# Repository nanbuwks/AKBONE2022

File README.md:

# AKBONE2022

秋葉原ロボット部のトレーニングボード。
2022リリースはLEDパネルキットです。

初期コンセプトとAlpha版の説明
「AKBONE2022 で LED パネルを使ったオープンソーストレーニングキットを考える」
https://qiita.com/nanbuwks/items/5271dedf196623d452a0

AVTOKYO2022で頒布したBeta1版の説明
「LEDパネルキットAKBONE2022で楽しもう！ Beta1版」
https://qiita.com/nanbuwks/items/4317031bdf3bdcfafbf8

AKBONE2022の開発環境構築
「LEDパネルキット AKBONE2022 の環境構築を自分でやってみる
https://qiita.com/nanbuwks/items/d4523ebfb9cabdae90c5

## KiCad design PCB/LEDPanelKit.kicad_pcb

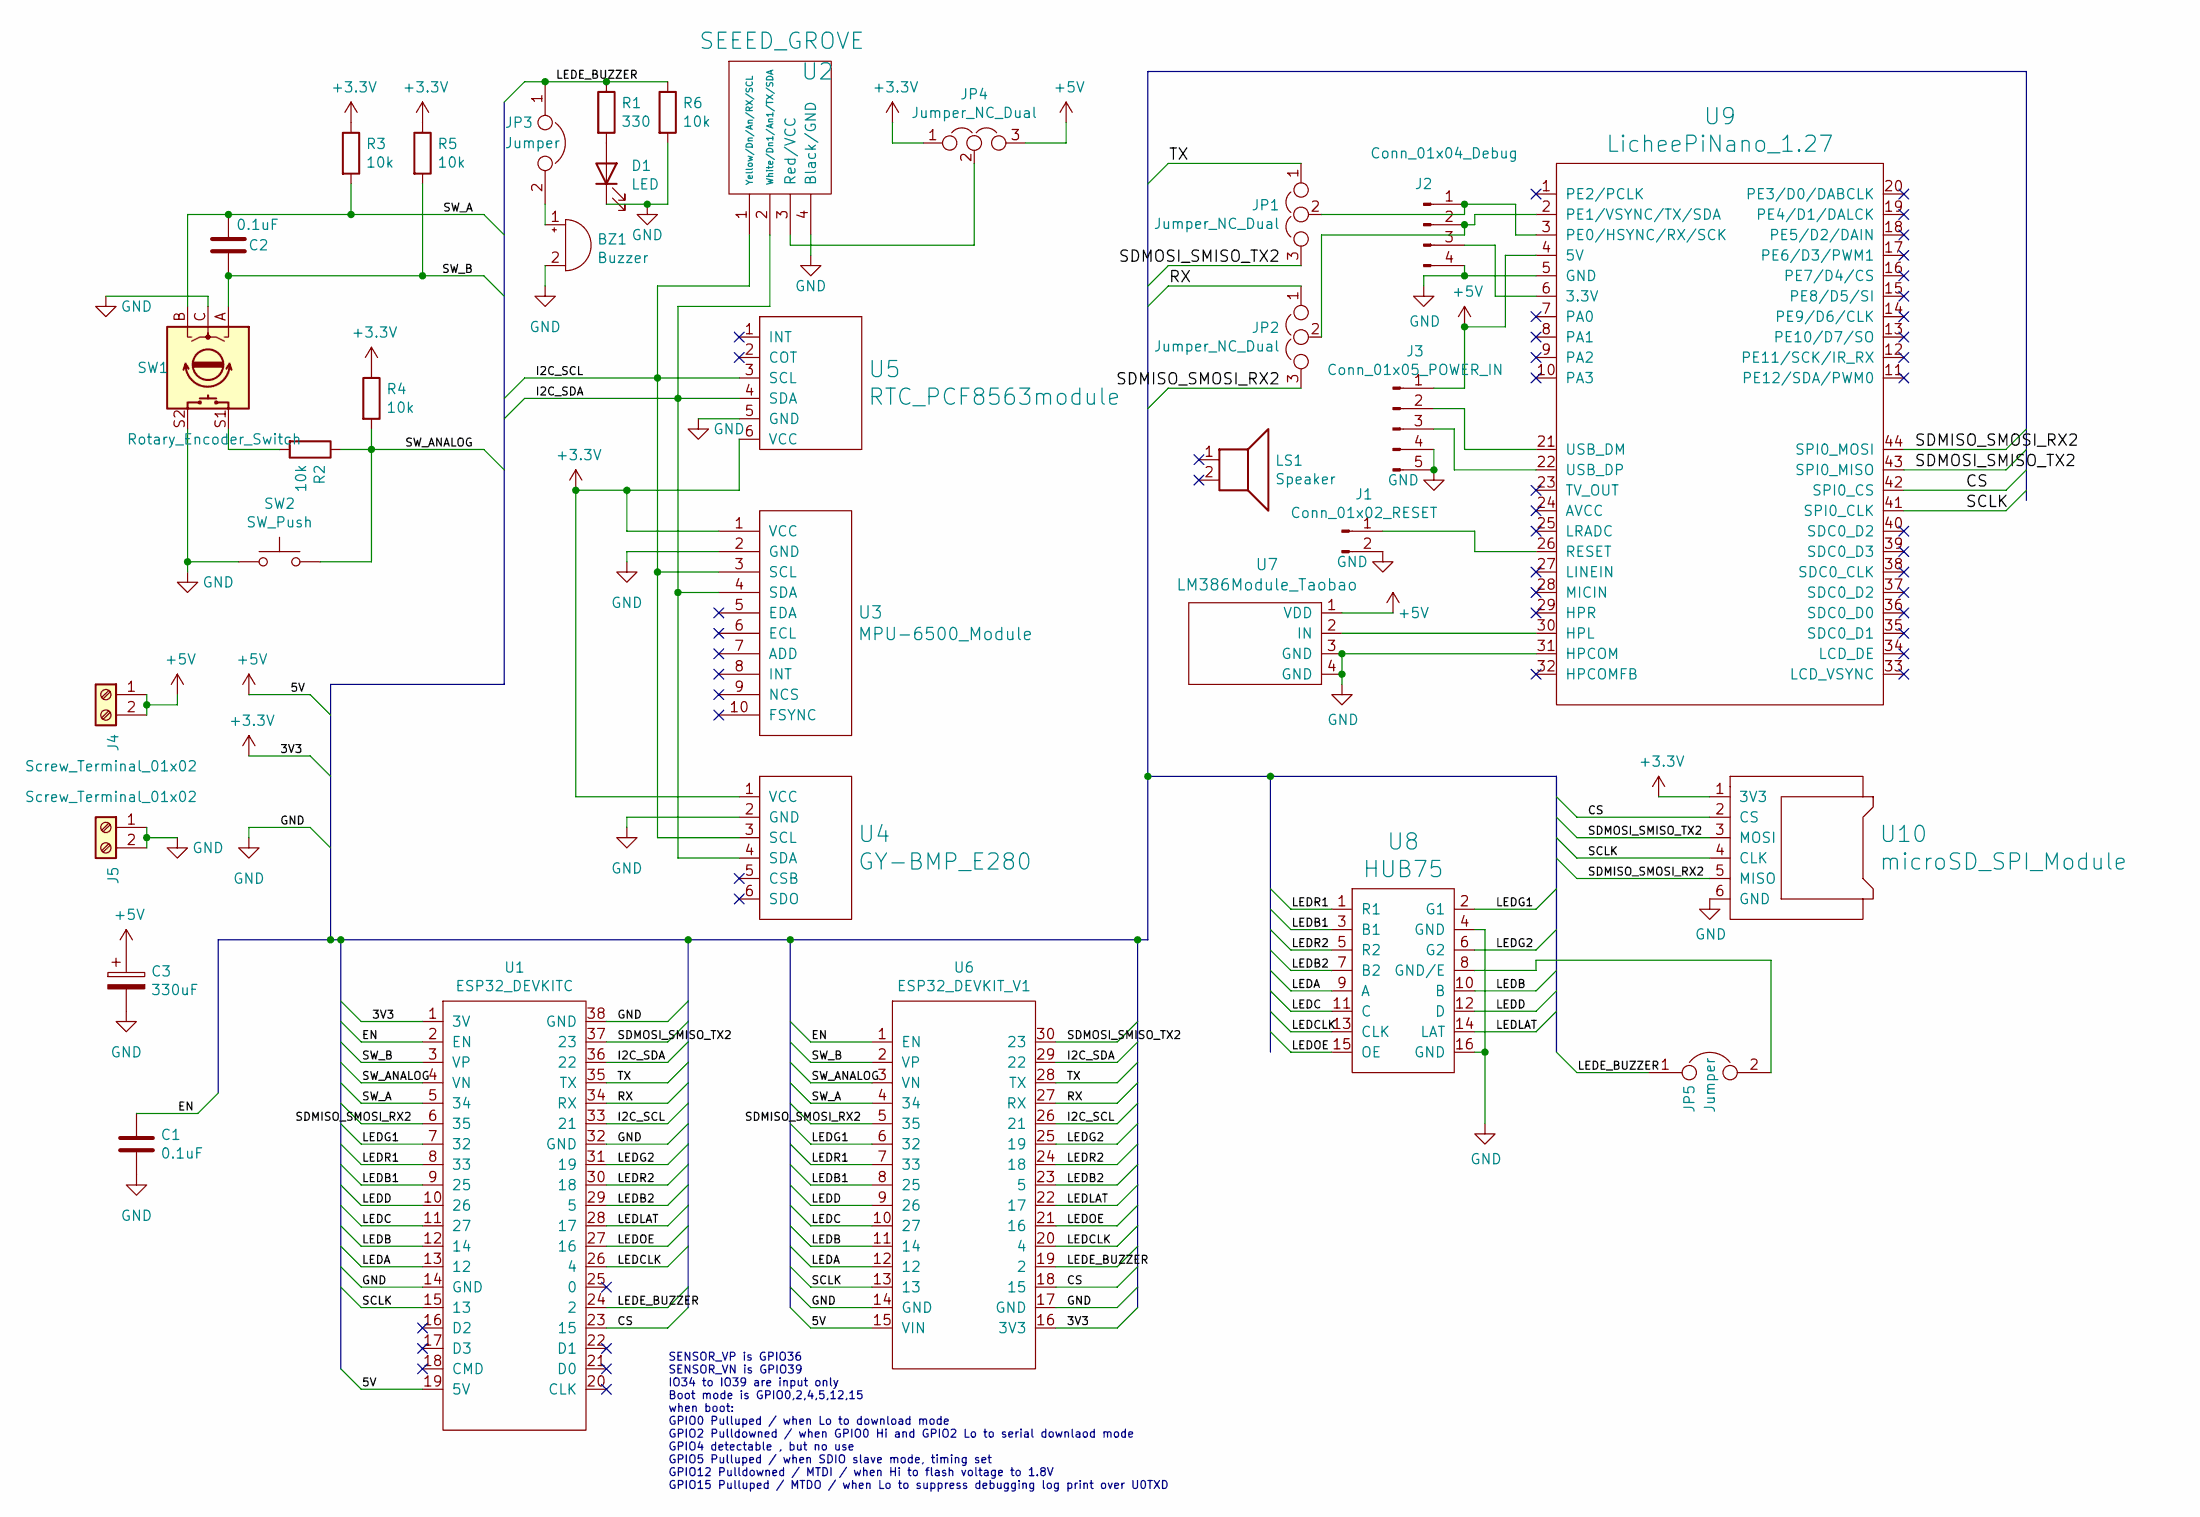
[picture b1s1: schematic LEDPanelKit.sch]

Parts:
BZ1: Buzzer; Buzzer_12x9.5RM7.6
C1, C2: 0.1uF; C_1206_3216Metric_Pad1.33x1.80mm_HandSolder
C3: 330uF; CP_Radial_D8.0mm_P5.00mm
D1: LED; LED_D5.0mm
J1: Conn_01x02_RESET; PinHeader_1x02_P2.54mm_Vertical
J2: Conn_01x04_Debug; PinHeader_1x04_P2.54mm_Vertical
J3: Conn_01x05_POWER_IN; PinHeader_1x05_P2.54mm_Vertical
J4, J5: Screw_Terminal_01x02; TerminalBlock_bornier-2_P5.08mm
JP1, JP2: Jumper_NC_Dual; PinHeader_1x03_P2.54mm_Vertical
JP3: Jumper; PinHeader_1x02_P2.54mm_Vertical
JP4: Jumper_NC_Dual; SolderJumper-3_P1.3mm_Bridged12_Pad1.0x1.5mm
JP5: Jumper; SolderJumper-2_P1.3mm_Open_TrianglePad1.0x1.5mm
LS1: Speaker; Speaker_Oval_2040
R1: 330; R_1206_3216Metric_Pad1.30x1.75mm_HandSolder
R2, R3, R4, R5, R6: 10k; R_1206_3216Metric_Pad1.30x1.75mm_HandSolder
SW1: Rotary_Encoder_Switch; RotaryEncoder_Alps_EC11E-Switch_Vertical_H20mm_CircularMoun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
SW2: SW_Push; SW_PUSH_6mm_H4.3mm
U1: ESP32_DEVKITC
U2: SEEED_GROVE; Seeedstudio_Grove_110990030_Vertical_4pin_2mmpitch
U3: MPU-6500_Module; MPU-6500_GY-6500
U4: GY-BMP_E280; GY_BMP_E280
U5: RTC_PCF8563module
U6: ESP32_DEVKIT_V1
U7: LM386Module_Taobao
U8: HUB75; IDC-Header_2x08_P2.54mm_Vertical
U9: LicheePiNano_1.27; Lichee_Pi_Nano
U10: microSD_SPI_Module; microSD_module_LCTechInc

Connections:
+3V3: JP4.1, R3.1, R4.1, R5.1, U1.1 (3V), U3.1 (VCC), U4.1 (VCC), U5.6 (VCC), U6.16 (3V3), U10.1 (3V3)
+5V: C3.1, J3.1, J4.1, J4.2, JP4.3, U1.19 (5V), U6.15 (VIN), U7.1 (VDD), U9.4 (5V)
/CS: U1.23 (15), U6.18 (15), U9.42 (SPI0_CS), U10.2 (CS)
/EN: C1.1, U1.2 (EN), U6.1 (EN)
/I2C_SCL: U1.33 (21), U2.1 (Yellow/Dn/An/RX/SCL), U3.3 (SCL), U4.3 (SCL), U5.3 (SCL), U6.26 (21)
/I2C_SDA: U1.36 (22), U2.2 (White/Dn1/An1/TX/SDA), U3.4 (SDA), U4.4 (SDA), U5.4 (SDA), U6.29 (22)
/LEDA: U1.13 (12), U6.12, U8.9 (A)
/LEDB: U1.12 (14), U6.11 (14), U8.10 (B)
/LEDB1: U1.9 (25), U6.8 (25), U8.3 (B1)
/LEDB2: U1.29 (5), U6.23 (5), U8.7 (B2)
/LEDC: U1.11 (27), U6.10 (27), U8.11 (C)
/LEDCLK: U1.26 (4), U6.20 (4), U8.13 (CLK)
/LEDD: U1.10 (26), U6.9 (26), U8.12 (D)
/LEDE_BUZZER: JP3.1, JP5.1, R1.1, R6.1, U1.24 (2), U6.19 (2)
/LEDG1: U1.7 (32), U6.6 (32), U8.2 (G1)
/LEDG2: U1.31 (19), U6.25 (19), U8.6 (G2)
/LEDLAT: U1.28 (17), U6.22 (17), U8.14 (LAT)
/LEDOE: U1.27 (16), U6.21 (16), U8.15 (OE)
/LEDR1: U1.8 (33), U6.7 (33), U8.1 (R1)
/LEDR2: U1.30 (18), U6.24 (18), U8.5 (R2)
/RX: JP2.1, U1.34 (RX), U6.27 (RX)
/SCLK: U1.15 (13), U6.13, U9.41 (SPI0_CLK), U10.4 (CLK)
/SDMISO_SMOSI_RX2: JP2.3, U1.6 (35), U6.5 (35), U9.44 (SPI0_MOSI), U10.5 (MISO)
/SDMOSI_SMISO_TX2: JP1.3, U1.37 (23), U6.30 (23), U9.43 (SPI0_MISO), U10.3 (MOSI)
/SW_A: C2.2, R3.2, SW1.B, U1.5 (34), U6.4 (34)
/SW_ANALOG: R2.1, R4.2, SW2.2, U1.4 (VN), U6.3 (VN)
/SW_B: C2.1, R5.2, SW1.A, U1.3 (VP), U6.2 (VP)
/TX: JP1.1, U1.35 (TX), U6.28 (TX)
GND: BZ1.2 (+), C1.2, C3.2, D1.1 (K), J1.2, J2.4, J3.4, J3.5, J5.1, J5.2, R6.2, SW1.C, SW1.S2, SW2.1, U1.14 (GND), U1.32 (GND), U1.38 (GND), U2.4 (Black/GND), U3.2 (GND), U4.2 (GND), U5.5 (GND), U6.14 (GND), U6.17 (GND), U7.3 (GND), U7.4 (GND), U8.4 (GND), U8.16 (GND), U9.5 (GND), U9.31 (HPCOM), U10.6 (GND)
unnamed: BZ1.1 (-), JP3.2
unnamed: D1.2 (A), R1.2
unnamed: J1.1, U9.26 (RESET)
unnamed: J2.1, JP1.2, U9.3 (PE0/HSYNC/RX/SCK)
unnamed: J2.2, JP2.2, U9.2 (PE1/VSYNC/TX/SDA)
unnamed: J2.3, U9.6 (3.3V)
unnamed: J3.2, U9.21 (USB_DM)
unnamed: J3.3, U9.22 (USB_DP)
unnamed: JP4.2, U2.3 (Red/VCC)
unnamed: JP5.2, U8.8 (GND/E)
unnamed: R2.2, SW1.S1
unnamed: U7.2 (IN), U9.30 (HPL)

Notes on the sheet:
SENSOR_VP is GPIO36 SENSOR_VN is GPIO39 IO34 to IO39 are input only Boot mode is GPIO0,2,4,5,12,15 when boot: GPIO0 Pulluped / when Lo to download mode GPIO2 Pulldowned / when GPIO0 Hi and GPIO2 Lo to serial downlaod mode GPIO4 detectable , but no use GPIO5 Pulluped / when SDIO slave mode, timing s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

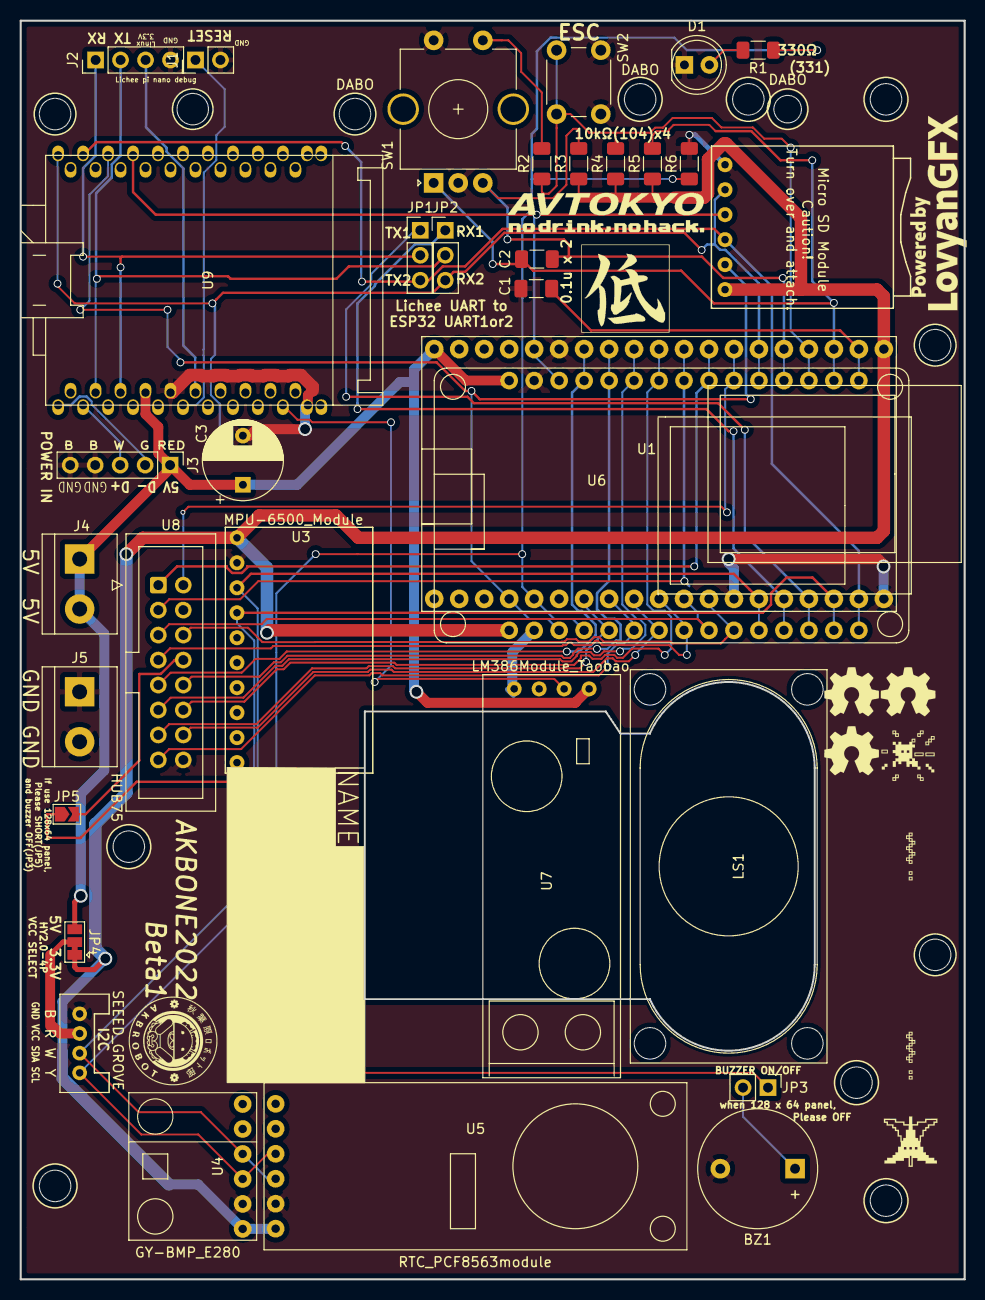
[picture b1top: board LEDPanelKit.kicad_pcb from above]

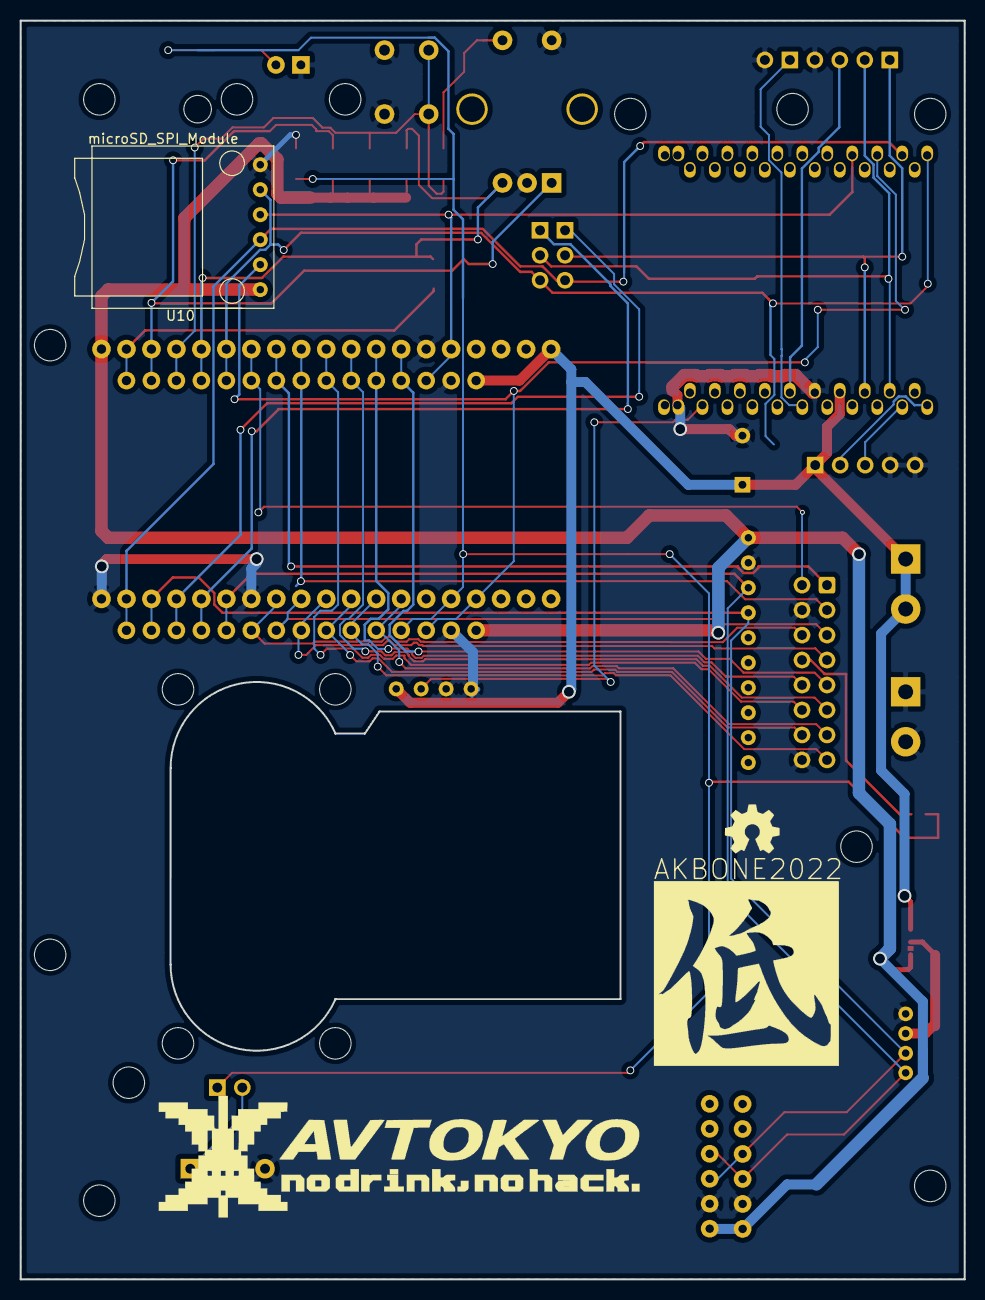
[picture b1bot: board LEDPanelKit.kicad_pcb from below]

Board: 2 copper layers, 96.0 x 128.0 mm, 38 parts (2 on the bottom side), 41 nets.

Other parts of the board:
OSHW: 1.1; OSHW_LOGL_SYLK_5mm
OSHW#2, OSHW#3, OSHW#4: 1.1; OSHW_LOGL_SYLK_5mm

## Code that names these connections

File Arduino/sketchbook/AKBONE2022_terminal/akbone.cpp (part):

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#include "akbone.hpp"
#if defined(USE_MPU6500) || defined(USE_RTC) || defined(BME280)
    #include <Wire.h>
    #define I2C_SDA 22
    #define I2C_SCL 21
#endif
#if defined(USE_ENCODER)
    #include <Ticker.h>
    #include <RotaryEncoder.h>
    #define SW_A    34
    #define SW_B    36
    #define BUTTON_SW1  39
    #define SW1_COUNT 2
    Ticker ticker1;
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    analogSetAttenuation(ADC_6db);  //ATT -6dB
    pinMode(BUTTON_SW1, INPUT);
    ticker1.attach_ms(20, check_button);
    attachInterrupt(digitalPinToInterrupt(SW_A), check_encoder, CHANGE);
    attachInterrupt(digitalPinToInterrupt(SW_B), check_encoder, CHANGE);
#endif
    //-------------------------------------------------------
    //	setup for TFCARD
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
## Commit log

2022-10-24 Alpha1
2022-11-05 Beta1 PCB
2022-11-05 add images / graphics directory
2022-11-05 add arduino sketchbook sample
2022-11-05 add avtokyo demo file
2022-11-05 modify for sample program for newest LovyanGFX library.
2022-11-06 modify sample program for LovyanGFX library develop branch 6aef99
2022-11-06 add BME280 sample sketch
2022-11-06 add RTC sample sketch
2022-11-06 AVTOKYO demo sketch missing fix
2022-11-06 GYRO demo sketch add
2022-11-08 add video sample
2022-11-08 video png file zip add
2022-11-12 SD_video addq
2022-11-14 add schematics pdf
2022-11-19 SD_video sketch verup for LovyanGFX new revision (86f0ea3wq)
2022-11-19 move ardublock developing code to testing folder.
2022-11-19 update sample programs to fit to LovyanGFX develop branch revision 86f0ea3
2022-11-19 add AKBON2020_terminal
2022-11-19 rename akbone2020_terminal
2022-11-19 rename directory name
2022-11-19 change README.md
2022-11-20 add akbone2020_news
2022-11-20 rename holder name to akbone2022_news
2022-11-20 akbone2022_news README.md説明追加
2022-11-20 証明書の説明追加
2022-12-10 Support P3 Panel
